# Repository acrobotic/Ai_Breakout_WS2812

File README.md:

Overview
---
This repository includes the Eagle design files (schematics and layout) for our [WS2812 Breakout Board][1]. The WS2812 is a 
Smart RGB LED with an embedded LED driver (WS2811) that needs only one data input line for controlling brightness and color. 
It represents the most compact solution for adding an RGB LED to a Microcontroller-powered project.

Example firmware files are included in this repository as well.

Product page
---
Please consider buying products from Acrobotic to help fund future Open-Source projects like this! We'll always put our best effort in every project, and release all our design files and code for you to use.

[Tutorials, technical details, and more information about this product can be found here: http://acrobotic.com/catalog/product/view/id/44][1]

License Information
---

All contents of this repository are licensed under a [Creative Commons Attribution-ShareAlike 3.0 Unported License](http://creativecommons.org/licenses/by-sa/3.0/).

[1]: http://acrobotic.com/catalog/product/view/id/44 "WS2812 Breakout Board"

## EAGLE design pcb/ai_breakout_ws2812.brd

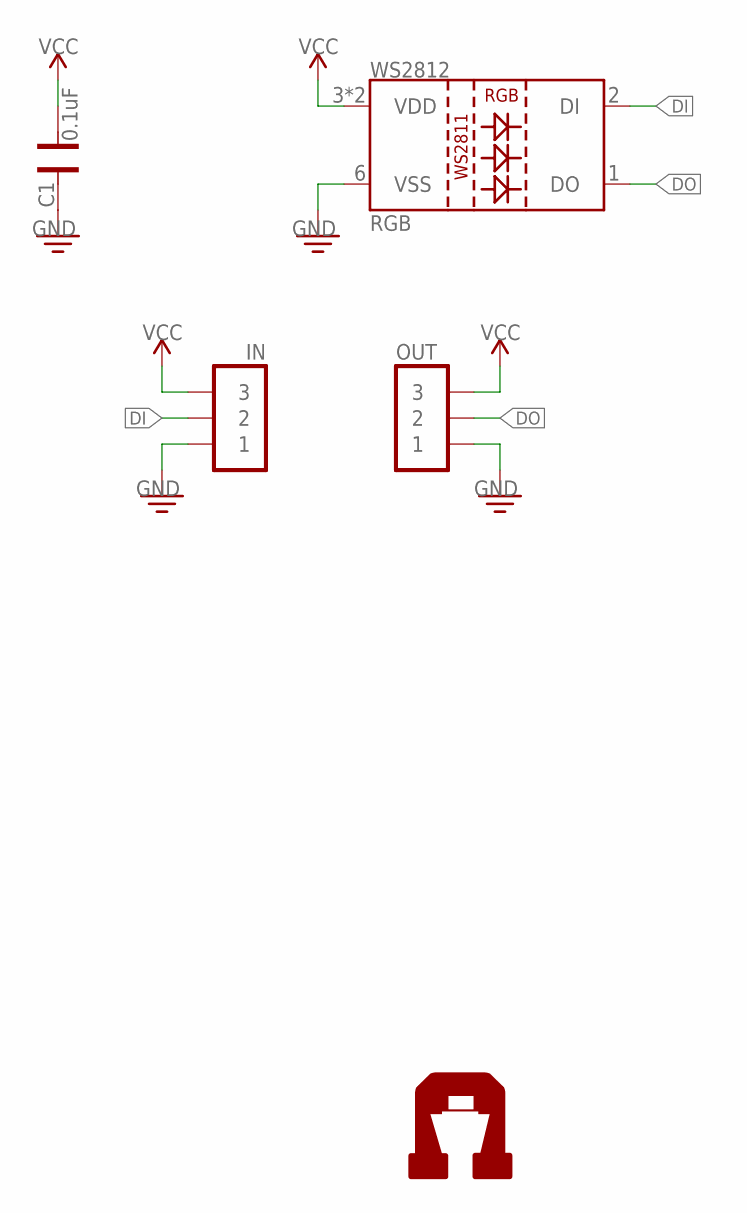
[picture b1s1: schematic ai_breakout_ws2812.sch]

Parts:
C1: 0.1uF; CAP-0603
IN: 1X03
OUT: 1X03
RGB: LED-WS2812
U$5: AI-LOGOL; AI-LOGO-L

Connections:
DI: IN.2, RGB.2 (DI)
DO: OUT.2, RGB.1 (DO)
GND: C1.2, IN.1, OUT.1, RGB.6 (VSS)
VCC: C1.1, IN.3, OUT.3, RGB.3 (VDD), RGB.5 (VDD)

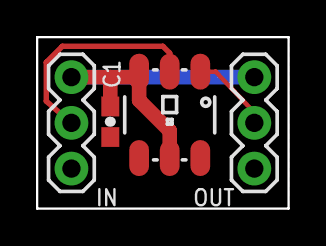
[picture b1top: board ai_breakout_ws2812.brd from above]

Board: 2 copper layers, 14.0 x 9.5 mm, 5 parts (1 on the bottom side), 4 nets.

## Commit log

2013-07-27 added a working example to the firmware.
2013-09-18 Minor modification to primer firmware.
2013-09-18 Modified silkscreen on the board.
2013-09-25 adding a simple demo for a rainbow effect.
2013-09-29 Corrected silkscreen widths, BOM, searchable PDF schematic.
2013-09-29 Deleted unwanted files.
2013-09-29 Create gh-pages branch via GitHub
2013-09-29 Added schematic file.
2013-09-29 Minor mod on wording.
2013-09-29 adding schematic (static) file.
2013-09-29 moving schematic file to a different directory.
2013-09-29 Minor wording mods.
2013-09-29 testing checking out schematic from master.
2013-09-29 testing (successfully) checking out schematic from master.
2013-09-29 Added static file for sample code.
2013-09-30 adding index.md for generating pages.
2013-09-30 switched to using our Github Pages template.
2013-09-30 minor change in stylesheet
2013-09-30 Minor changes to index page
2013-09-30 removed assets and plugins folder so that we use the ones from the user repo.
2013-09-30 changing fork me link
2013-10-04 Updateded index and .pdf file.
2013-10-04 Minor modifications. Version is now 1.1.
2013-10-04 Minor mod to BOM.xls
2013-10-04 Updated pdf version of schematic
2013-10-04 updating schematic pdf
2013-10-04 updating schematic pdf (non-vector font)
2013-10-05 Minor formatting change of BOM.
2013-10-25 Centered pins.
2014-01-30 Adding the bitbang firmware
2014-02-21 update firmware
